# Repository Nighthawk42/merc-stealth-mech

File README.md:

# merc-stealth-mech
 A modernization of the SteelSeries Merc Stealth Keyboard designed for use with mechanical switches.

Update: 24 February 2024 - This project was only ever intended as a proof-of-concept. There is a good chance that it will not work, and you should avoid prototyping using the files as-is. They likely need a great deal of work.

With that said, the project is being archived. If you are interested in a mechanical replacement for the Merc Stealth, I highly suggest looking at the Ergo Strafer by the folks over at Custom MK.

https://shop.custommk.com/collections/ergostrafer/products/ergostrafer

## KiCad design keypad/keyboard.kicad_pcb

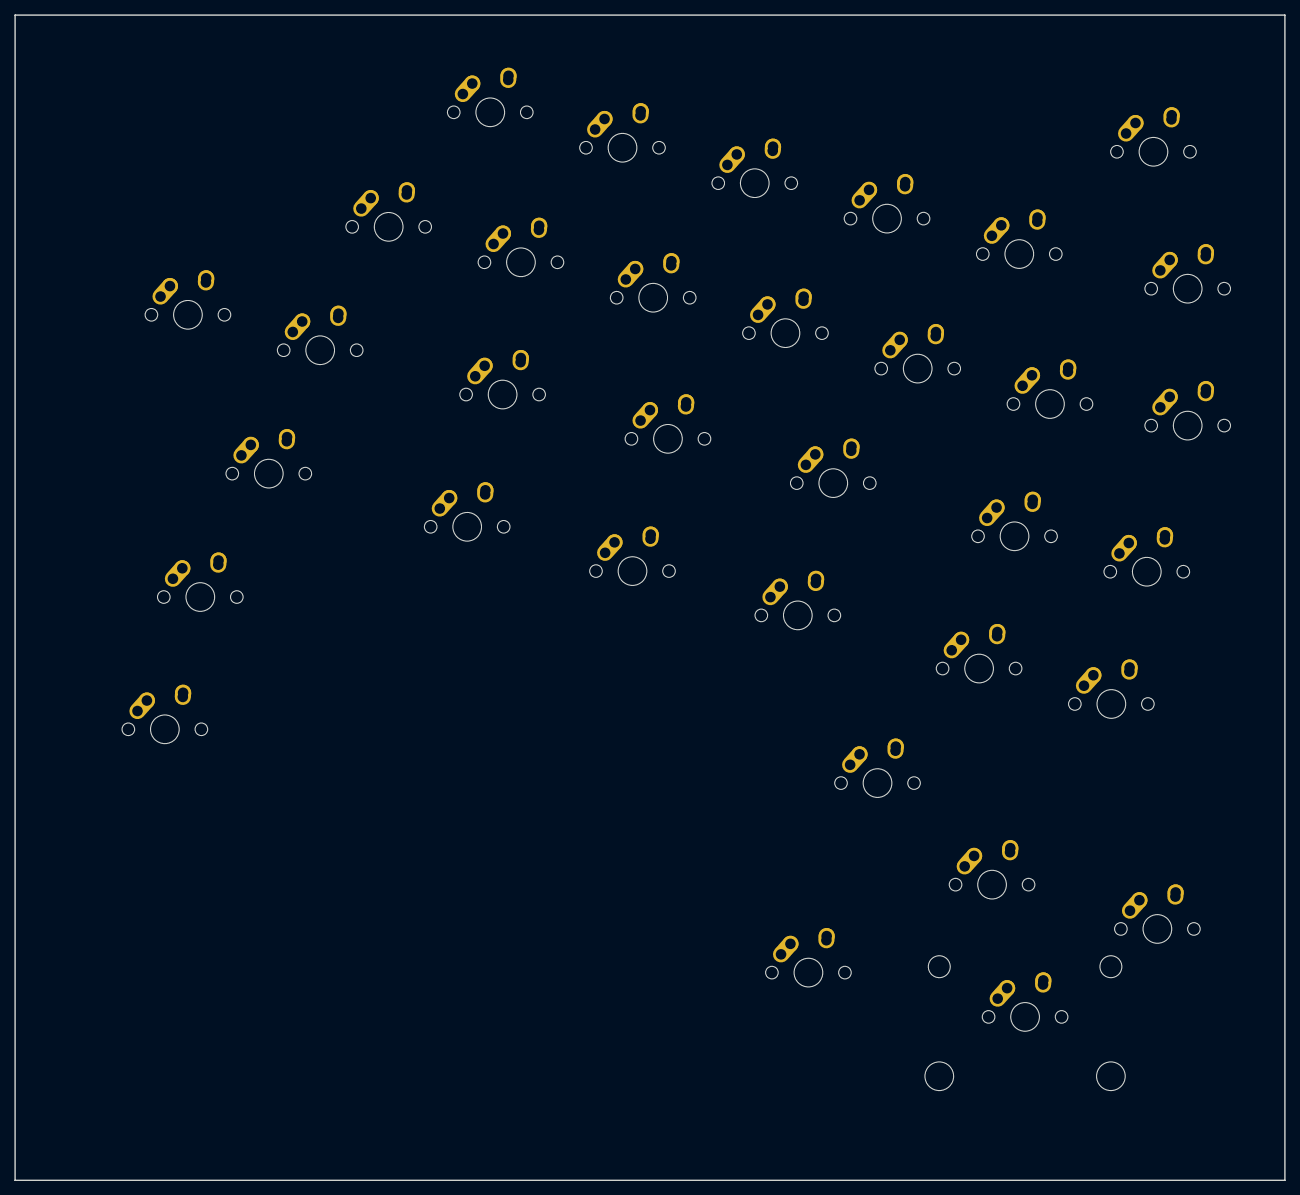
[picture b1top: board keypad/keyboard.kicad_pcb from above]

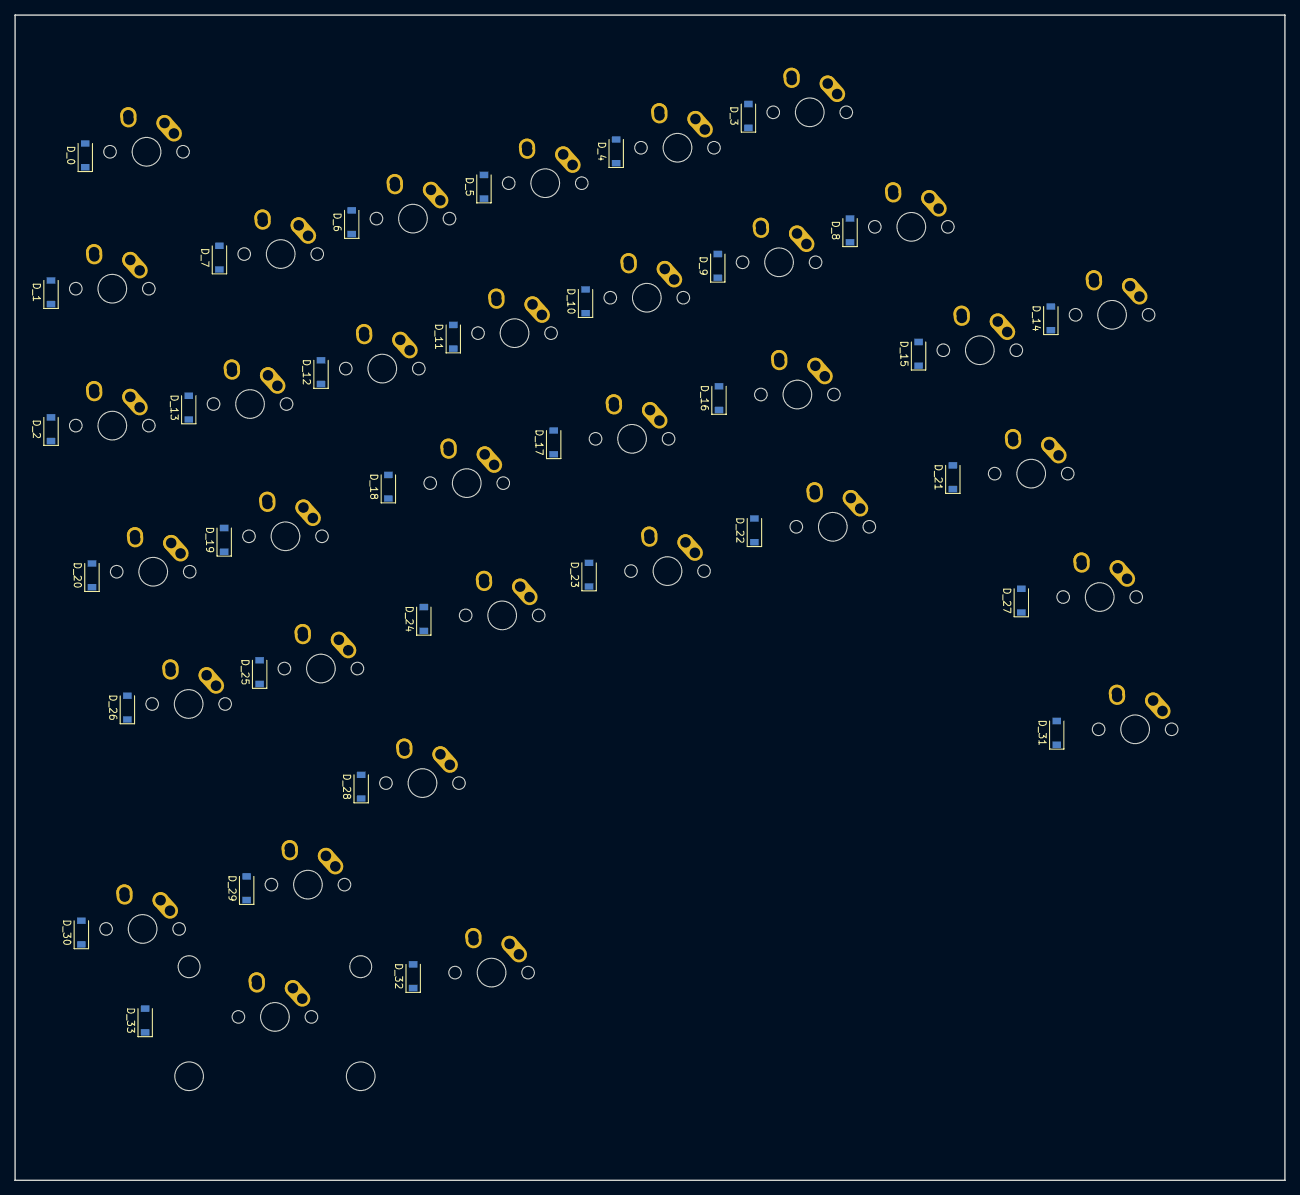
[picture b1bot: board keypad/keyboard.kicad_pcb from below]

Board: 2 copper layers, 176.7 x 162.1 mm, 68 parts (34 on the bottom side), 50 nets, no tracks yet.

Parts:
D_0, D_1, D_2, D_3, D_4, D_5, D_6, D_7, D_8, D_9, D_10, D_11, D_12, D_13, D_14, D_15, D_16, D_17, D_18, D_19, D_20, D_21, D_22, D_23, D_24, D_25, D_26, D_27, D_28, D_29, D_30, D_31, D_32, D_33: D; D_SOD-123
K_0, K_1, K_2, K_3, K_4, K_5, K_6, K_7, K_8, K_9, K_10, K_11, K_12, K_13, K_14, K_15, K_19, K_20, K_25, K_26, K_28, K_29, K_30: KEYSW; MX-1U-NoLED
K_16, K_17, K_18, K_21, K_22, K_23, K_24, K_27, K_31, K_32: KEYSW; MX-1.25U-NoLED
K_33: KEYSW; MX-2U-NoLED

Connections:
unnamed: D_0.2, K_0.2
unnamed: D_1.2, K_1.2
unnamed: D_2.2, K_2.2
unnamed: D_3.2, K_3.2
unnamed: D_4.2, K_4.2
unnamed: D_5.2, K_5.2
unnamed: D_6.2, K_6.2
unnamed: D_7.2, K_7.2
unnamed: D_8.2, K_8.2
unnamed: D_9.2, K_9.2
unnamed: D_10.2, K_10.2
unnamed: D_11.2, K_11.2
unnamed: D_12.2, K_12.2
unnamed: D_13.2, K_13.2
unnamed: D_14.2, K_14.2
unnamed: D_15.2, K_15.2
unnamed: D_16.2, K_16.2
unnamed: D_17.2, K_17.2
unnamed: D_18.2, K_18.2
unnamed: D_19.2, K_19.2
unnamed: D_20.2, K_20.2
unnamed: D_21.2, K_21.2
unnamed: D_22.2, K_22.2
unnamed: D_23.2, K_23.2
unnamed: D_24.2, K_24.2
unnamed: D_25.2, K_25.2
unnamed: D_26.2, K_26.2
unnamed: D_27.2, K_27.2
unnamed: D_28.2, K_28.2
unnamed: D_29.2, K_29.2
unnamed: D_30.2, K_30.2
unnamed: D_31.2, K_31.2
unnamed: D_32.2, K_32.2
unnamed: D_33.2, K_33.2
col0: K_14.1, K_27.1, K_31.1
col1: K_15.1, K_21.1
col2: K_8.1, K_22.1
col3: K_3.1, K_9.1, K_16.1
col4: K_4.1, K_10.1, K_17.1, K_23.1
col5: K_5.1, K_11.1, K_18.1, K_24.1, K_28.1, K_32.1
col6: K_6.1, K_7.1, K_12.1, K_19.1, K_25.1, K_29.1
col7: K_13.1, K_20.1, K_26.1, K_30.1, K_33.1
col8: K_0.1, K_1.1, K_2.1
row0: D_0.1, D_3.1, D_4.1
row1: D_1.1, D_5.1, D_6.1, D_7.1, D_8.1, D_9.1, D_10.1
row2: D_2.1, D_11.1, D_12.1, D_13.1, D_14.1, D_15.1, D_16.1
row3: D_17.1, D_18.1, D_19.1, D_20.1, D_21.1, D_22.1, D_23.1
row4: D_24.1, D_25.1, D_26.1, D_27.1
row5: D_28.1, D_31.1
row6: D_29.1, D_30.1, D_32.1

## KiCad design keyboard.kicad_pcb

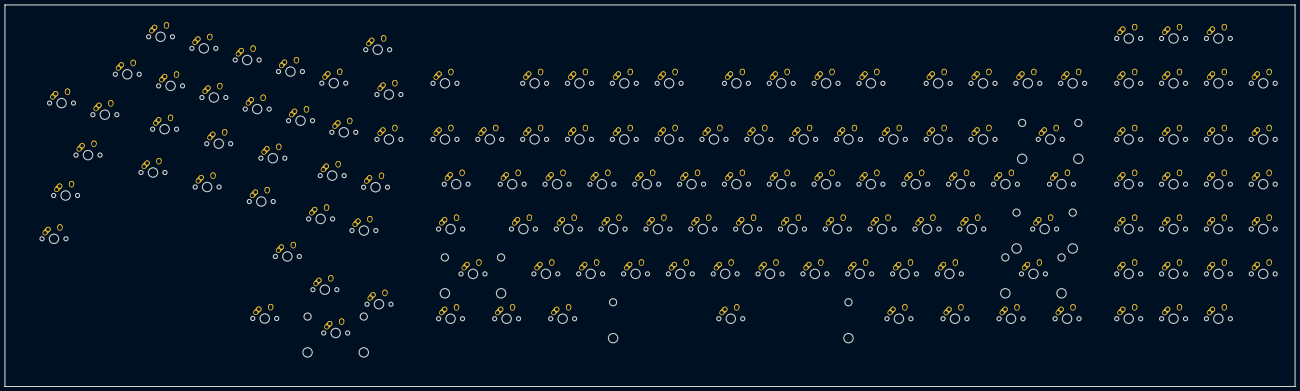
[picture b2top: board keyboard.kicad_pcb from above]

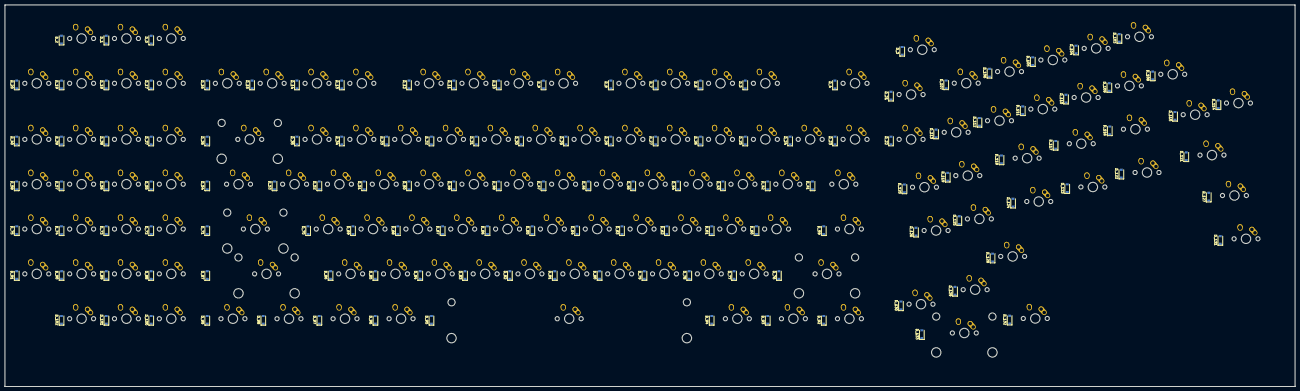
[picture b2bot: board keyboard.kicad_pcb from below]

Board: 2 copper layers, 548.1 x 162.1 mm, 268 parts (134 on the bottom side), 169 nets, no tracks yet.

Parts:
D_0, D_1, D_2, D_3, D_4, D_5, D_6, D_7, D_8, D_9, D_10, D_11, D_12, D_13, D_14, D_15, D_16, D_17, D_18, D_19, D_20, D_21, D_22, D_23, D_24, D_25, D_26, D_27, D_28, D_29, D_30, D_31, D_32, D_33, D_34, D_35, D_36, D_37, D_38, D_39, D_40, D_41, D_42, D_43, D_44, D_45, D_46, D_47, D_48, D_49, D_50, D_51, D_52, D_53, D_54, D_55, D_56, D_57, D_58, D_59, D_60, D_61, D_62, D_63, D_64, D_65, D_66, D_67, D_68, D_69, D_70, D_71, D_72, D_73, D_74, D_75, D_76, D_77, D_78, D_79, D_80, D_81, D_82, D_83, D_84, D_85, D_86, D_87, D_88, D_89, D_90, D_91, D_92, D_93, D_94, D_95, D_96, D_97, D_98, D_99, D_100, D_101, D_102, D_103, D_104, D_105, D_106, D_107, D_108, D_109, D_110, D_111, D_112, D_113, D_114, D_115, D_116, D_117, D_118, D_119, D_120, D_121, D_122, D_123, D_124, D_125, D_126, D_127, D_128, D_129, D_130, D_131, D_132, D_133: D; D_SOD-123
K_0, K_1, K_2, K_3, K_4, K_5, K_6, K_7, K_8, K_9, K_10, K_11, K_12, K_13, K_14, K_15, K_16, K_17, K_18, K_19, K_20, K_21, K_22, K_23, K_24, K_25, K_26, K_27, K_28, K_29, K_30, K_31, K_32, K_33, K_34, K_35, K_37, K_38, K_39, K_40, K_42, K_43, K_44, K_45, K_46, K_47, K_48, K_49, K_50, K_51, K_52, K_53, K_55, K_56, K_57, K_58, K_60, K_61, K_62, K_63, K_64, K_65, K_66, K_67, K_68, K_69, K_70, K_72, K_73, K_74, K_75, K_77, K_78, K_79, K_80, K_81, K_82, K_83, K_84, K_85, K_86, K_88, K_89, K_90, K_91, K_100, K_101, K_102, K_103, K_104, K_105, K_106, K_107, K_108, K_109, K_110, K_111, K_112, K_113, K_114, K_115, K_119, K_120, K_125, K_126, K_128, K_129, K_130: KEYSW; MX-1U-NoLED
K_36, K_133: KEYSW; MX-2U-NoLED
K_41, K_54: KEYSW; MX-1.5U-NoLED
K_59, K_92, K_93, K_94, K_96, K_97, K_98, K_99, K_116, K_117, K_118, K_121, K_122, K_123, K_124, K_127, K_131, K_132: KEYSW; MX-1.25U-NoLED
K_71, K_76: KEYSW; MX-2.25U-NoLED
K_87: KEYSW; MX-2.75U-NoLED
K_95: KEYSW; MX-6.25U-NoLED

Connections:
unnamed: D_0.2, K_0.2
unnamed: D_1.2, K_1.2
unnamed: D_2.2, K_2.2
unnamed: D_3.2, K_3.2
unnamed: D_4.2, K_4.2
unnamed: D_5.2, K_5.2
unnamed: D_6.2, K_6.2
unnamed: D_7.2, K_7.2
unnamed: D_8.2, K_8.2
unnamed: D_9.2, K_9.2
unnamed: D_10.2, K_10.2
unnamed: D_11.2, K_11.2
unnamed: D_12.2, K_12.2
unnamed: D_13.2, K_13.2
unnamed: D_14.2, K_14.2
unnamed: D_15.2, K_15.2
unnamed: D_16.2, K_16.2
unnamed: D_17.2, K_17.2
unnamed: D_18.2, K_18.2
unnamed: D_19.2, K_19.2
unnamed: D_20.2, K_20.2
unnamed: D_21.2, K_21.2
unnamed: D_22.2, K_22.2
unnamed: D_23.2, K_23.2
unnamed: D_24.2, K_24.2
unnamed: D_25.2, K_25.2
unnamed: D_26.2, K_26.2
unnamed: D_27.2, K_27.2
unnamed: D_28.2, K_28.2
unnamed: D_29.2, K_29.2
unnamed: D_30.2, K_30.2
unnamed: D_31.2, K_31.2
unnamed: D_32.2, K_32.2
unnamed: D_33.2, K_33.2
unnamed: D_34.2, K_34.2
unnamed: D_35.2, K_35.2
unnamed: D_36.2, K_36.2
unnamed: D_37.2, K_37.2
unnamed: D_38.2, K_38.2
unnamed: D_39.2, K_39.2
unnamed: D_40.2, K_40.2
unnamed: D_41.2, K_41.2
unnamed: D_42.2, K_42.2
unnamed: D_43.2, K_43.2
unnamed: D_44.2, K_44.2
unnamed: D_45.2, K_45.2
unnamed: D_46.2, K_46.2
unnamed: D_47.2, K_47.2
unnamed: D_48.2, K_48.2
unnamed: D_49.2, K_49.2
unnamed: D_50.2, K_50.2
unnamed: D_51.2, K_51.2
unnamed: D_52.2, K_52.2
unnamed: D_53.2, K_53.2
unnamed: D_54.2, K_54.2
unnamed: D_55.2, K_55.2
unnamed: D_56.2, K_56.2
unnamed: D_57.2, K_57.2
unnamed: D_58.2, K_58.2
unnamed: D_59.2, K_59.2
unnamed: D_60.2, K_60.2
unnamed: D_61.2, K_61.2
unnamed: D_62.2, K_62.2
unnamed: D_63.2, K_63.2
unnamed: D_64.2, K_64.2
unnamed: D_65.2, K_65.2
unnamed: D_66.2, K_66.2
unnamed: D_67.2, K_67.2
unnamed: D_68.2, K_68.2
unnamed: D_69.2, K_69.2
unnamed: D_70.2, K_70.2
unnamed: D_71.2, K_71.2
unnamed: D_72.2, K_72.2
unnamed: D_73.2, K_73.2
unnamed: D_74.2, K_74.2
unnamed: D_75.2, K_75.2
unnamed: D_76.2, K_76.2
unnamed: D_77.2, K_77.2
unnamed: D_78.2, K_78.2
unnamed: D_79.2, K_79.2
unnamed: D_80.2, K_80.2
unnamed: D_81.2, K_81.2
unnamed: D_82.2, K_82.2
unnamed: D_83.2, K_83.2
unnamed: D_84.2, K_84.2
unnamed: D_85.2, K_85.2
unnamed: D_86.2, K_86.2
unnamed: D_87.2, K_87.2
unnamed: D_88.2, K_88.2
unnamed: D_89.2, K_89.2
unnamed: D_90.2, K_90.2
unnamed: D_91.2, K_91.2
unnamed: D_92.2, K_92.2
unnamed: D_93.2, K_93.2
unnamed: D_94.2, K_94.2
unnamed: D_95.2, K_95.2
unnamed: D_96.2, K_96.2
unnamed: D_97.2, K_97.2
unnamed: D_98.2, K_98.2
unnamed: D_99.2, K_99.2
unnamed: D_100.2, K_100.2
unnamed: D_101.2, K_101.2
unnamed: D_102.2, K_102.2
unnamed: D_103.2, K_103.2
unnamed: D_104.2, K_104.2
unnamed: D_105.2, K_105.2
unnamed: D_106.2, K_106.2
unnamed: D_107.2, K_107.2
unnamed: D_108.2, K_108.2
unnamed: D_109.2, K_109.2
unnamed: D_110.2, K_110.2
unnamed: D_111.2, K_111.2
unnamed: D_112.2, K_112.2
unnamed: D_113.2, K_113.2
unnamed: D_114.2, K_114.2
unnamed: D_115.2, K_115.2
unnamed: D_116.2, K_116.2
unnamed: D_117.2, K_117.2
unnamed: D_118.2, K_118.2
unnamed: D_119.2, K_119.2
unnamed: D_120.2, K_120.2
unnamed: D_121.2, K_121.2
unnamed: D_122.2, K_122.2
unnamed: D_123.2, K_123.2
unnamed: D_124.2, K_124.2
unnamed: D_125.2, K_125.2
unnamed: D_126.2, K_126.2
unnamed: D_127.2, K_127.2
unnamed: D_128.2, K_128.2
unnamed: D_129.2, K_129.2
unnamed: D_130.2, K_130.2
unnamed: D_131.2, K_131.2
unnamed: D_132.2, K_132.2
unnamed: D_133.2, K_133.2
col0: K_114.1, K_127.1, K_131.1
col1: K_115.1, K_121.1
col2: K_108.1, K_122.1
col3: K_103.1, K_109.1, K_116.1
col4: K_104.1, K_110.1, K_117.1, K_123.1
col5: K_105.1, K_111.1, K_118.1, K_124.1, K_128.1, K_132.1
col6: K_106.1, K_107.1, K_112.1, K_119.1, K_125.1, K_129.1
col7: K_113.1, K_120.1, K_126.1, K_130.1, K_133.1
col8: K_3.1, K_21.1, K_22.1
col9: K_4.1, K_23.1, K_41.1, K_59.1, K_92.1
col10: K_24.1, K_76.1, K_93.1
col11: K_5.1, K_25.1, K_42.1, K_60.1, K_77.1
col12: K_6.1, K_26.1, K_43.1, K_61.1, K_78.1, K_94.1
col13: K_7.1, K_27.1, K_44.1, K_62.1, K_79.1
col14: K_8.1, K_28.1, K_45.1, K_63.1, K_80.1
col15: K_29.1, K_46.1, K_64.1, K_81.1, K_95.1
col16: K_9.1, K_30.1, K_47.1, K_65.1, K_82.1
col17: K_10.1, K_31.1, K_48.1, K_66.1, K_83.1
col18: K_11.1, K_32.1, K_49.1, K_67.1, K_84.1
col19: K_12.1, K_33.1, K_50.1, K_68.1, K_85.1, K_96.1
col20: K_13.1, K_34.1, K_51.1, K_69.1, K_86.1, K_97.1
col21: K_14.1, K_35.1, K_52.1, K_70.1
col22: K_15.1, K_53.1, K_71.1, K_87.1, K_98.1
col23: K_16.1, K_36.1, K_54.1, K_99.1
col24: K_0.1, K_17.1, K_37.1, K_55.1, K_72.1, K_88.1, K_100.1
col25: K_1.1, K_18.1, K_38.1, K_56.1, K_73.1, K_89.1, K_101.1
col26: K_2.1, K_19.1, K_39.1, K_57.1, K_74.1, K_90.1, K_102.1
col27: K_20.1, K_40.1, K_58.1, K_75.1, K_91.1
row0: D_0.1, D_1.1, D_2.1, D_3.1, D_103.1, D_104.1
row1: D_4.1, D_5.1, D_6.1, D_7.1, D_8.1, D_9.1, D_10.1, D_11.1, D_12.1, D_13.1, D_14.1, D_15.1, D_16.1, D_17.1, D_18.1, D_19.1, D_20.1, D_21.1, D_105.1, D_106.1, D_107.1, D_108.1, D_109.1, D_110.1
row2: D_22.1, D_23.1, D_24.1, D_25.1, D_26.1, D_27.1, D_28.1, D_29.1, D_30.1, D_31.1, D_32.1, D_33.1, D_34.1, D_35.1, D_36.1, D_37.1, D_38.1, D_39.1, D_40.1, D_111.1, D_112.1, D_113.1, D_114.1, D_115.1, D_116.1
row3: D_41.1, D_42.1, D_43.1, D_44.1, D_45.1, D_46.1, D_47.1, D_48.1, D_49.1, D_50.1, D_51.1, D_52.1, D_53.1, D_54.1, D_55.1, D_56.1, D_57.1, D_58.1, D_117.1, D_118.1, D_119.1, D_120.1, D_121.1, D_122.1, D_123.1
row4: D_59.1, D_60.1, D_61.1, D_62.1, D_63.1, D_64.1, D_65.1, D_66.1, D_67.1, D_68.1, D_69.1, D_70.1, D_71.1, D_72.1, D_73.1, D_74.1, D_75.1, D_124.1, D_125.1, D_126.1, D_127.1
row5: D_76.1, D_77.1, D_78.1, D_79.1, D_80.1, D_81.1, D_82.1, D_83.1, D_84.1, D_85.1, D_86.1, D_87.1, D_88.1, D_89.1, D_90.1, D_128.1, D_131.1
row6: D_91.1, D_92.1, D_93.1, D_94.1, D_95.1, D_96.1, D_97.1, D_98.1, D_99.1, D_100.1, D_101.1, D_102.1, D_129.1, D_130.1, D_132.1

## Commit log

2020-08-29 Revision 1
2020-08-31 Rev. 2
    Keypad-only version added.
